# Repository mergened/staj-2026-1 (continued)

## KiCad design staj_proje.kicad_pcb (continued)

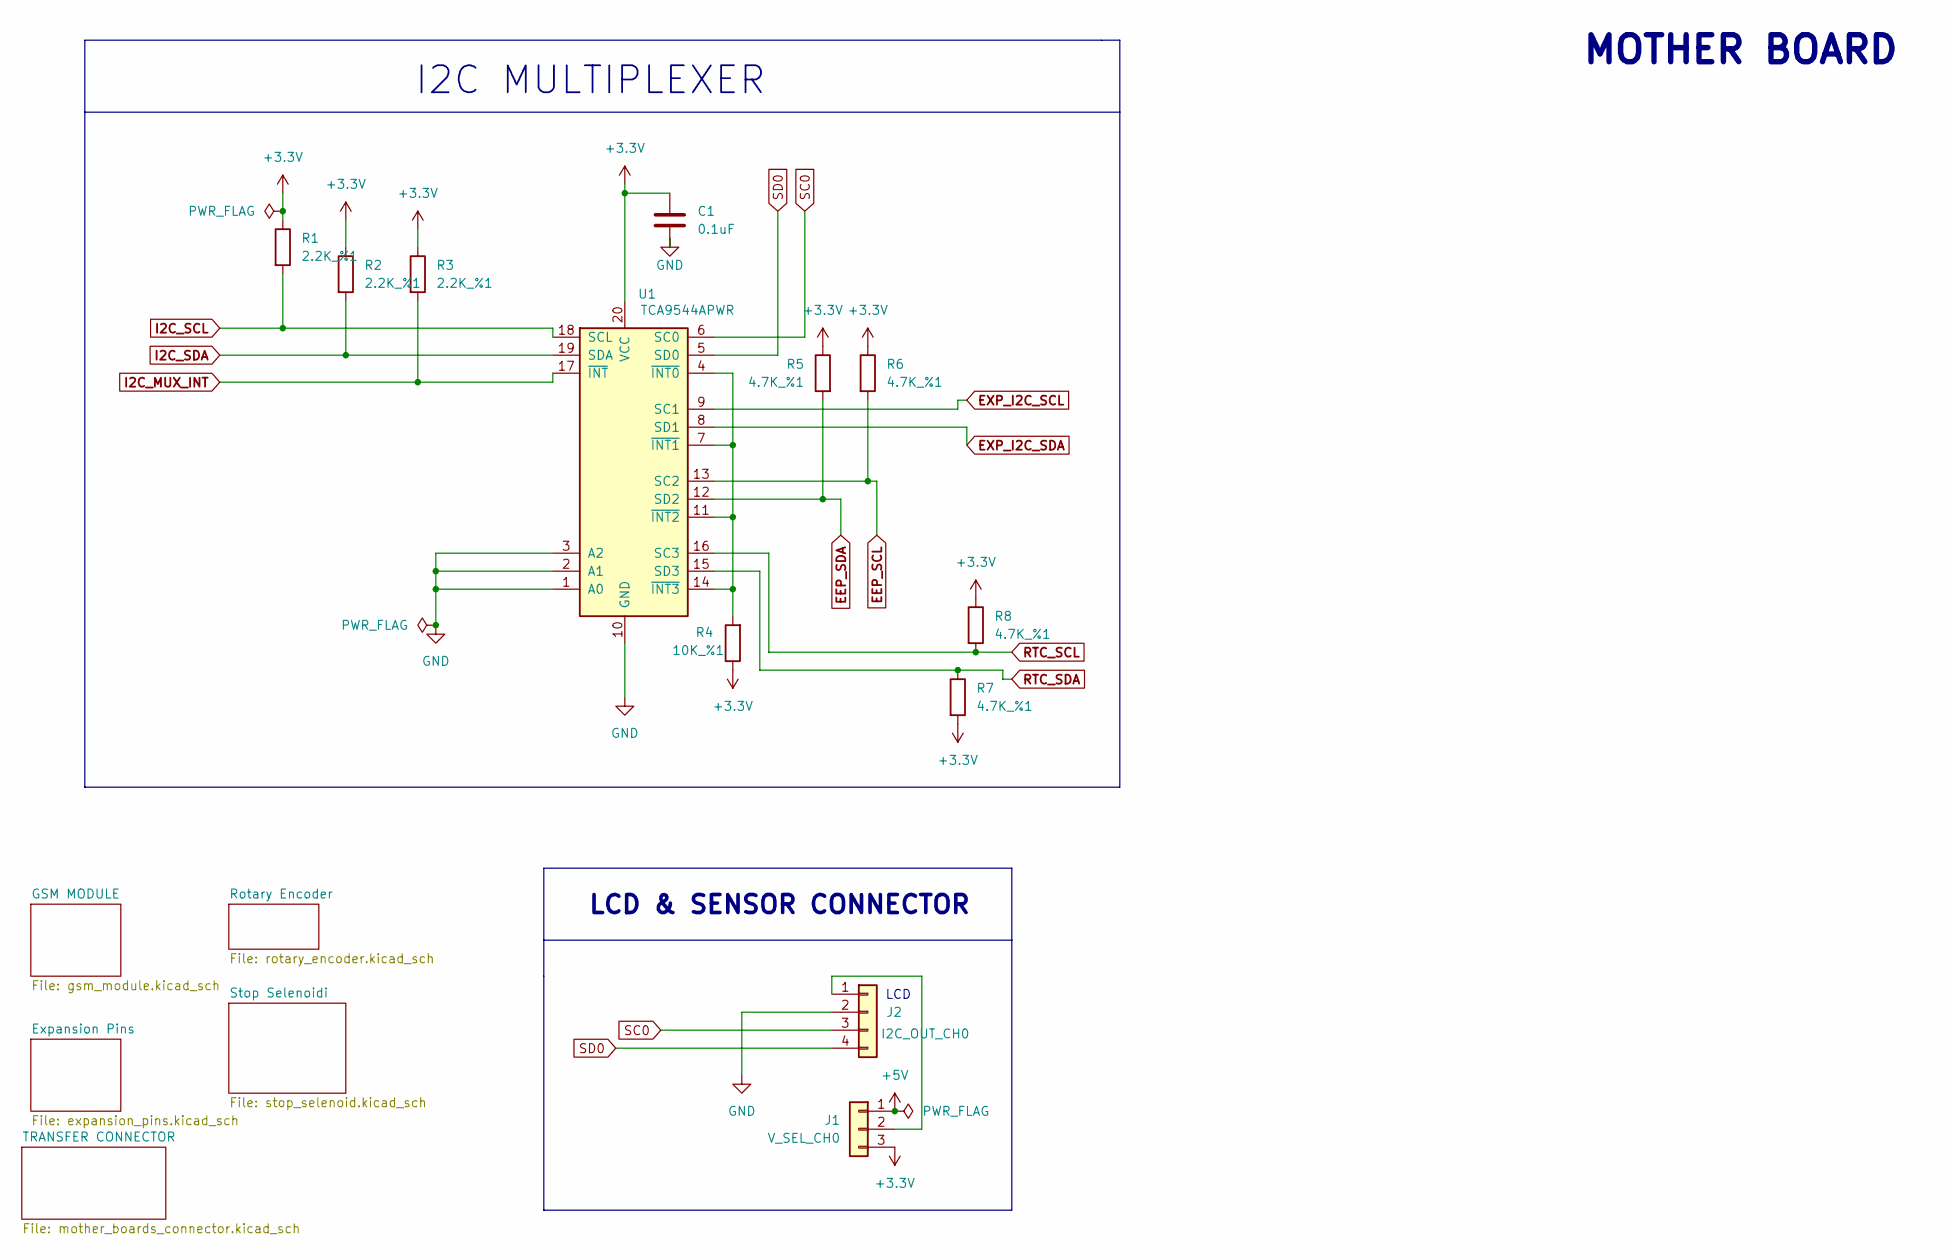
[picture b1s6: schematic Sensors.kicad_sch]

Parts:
C1: 0.1uF; C_0603_1608Metric; Manufacturer PN C0603C104K5RACTU; Digikey 399-C0603C104K5RACTUCT-ND
J1: V_SEL_CH0; PinHeader_1x03_P2.54mm_Vertical; Manufacturer PN G800W305018EU; Digikey 664-G800W305018EU-ND
J2: I2C_OUT_CH0; PinHeader_1x04_P2.54mm_Vertical; Manufacturer PN 10129378-904002BLF; Digikey 10129378-904002BLF-ND
R1, R2, R3: 2.2K_%1; R_0603_1608Metric; Manufacturer PN RC0603FR-072K2L; Digikey 311-2.20KHRCT-ND
R4: 10K_%1; R_0603_1608Metric; Manufacturer PN RC0603FR-0710KL; Digikey 311-10.0KHRCT-ND
R5, R6, R7, R8: 4.7K_%1; R_0603_1608Metric; Manufacturer PN RC0603FR-074K7L; Digikey 311-4.70KHRCT-ND
U1: TCA9544APWR; TSSOP-20_4.4x6.5mm_P0.65mm; Manufacturer PN TCA9544APWR; Digikey 296-40576-1-ND

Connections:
+3.3V: C1.1, J1.3, R1.1, R2.1, R3.1, R4.1, R5.1, R6.1, R7.2, R8.1, U1.20 (VCC); also elsewhere on the board
+5V: J1.1; also elsewhere on the board
EEP_SCL: R6.2, U1.13 (SC2); also elsewhere on the board
EEP_SDA: R5.2, U1.12 (SD2); also elsewhere on the board
EXP_I2C_SCL: U1.9 (SC1); also elsewhere on the board
EXP_I2C_SDA: U1.8 (SD1); also elsewhere on the board
GND: C1.2, J2.2, U1.1 (A0), U1.2 (A1), U1.3 (A2), U1.10 (GND); also elsewhere on the board
I2C_MUX_INT: R3.2, U1.17 (~INT); also elsewhere on the board
I2C_SCL: R1.2, U1.18 (SCL); also elsewhere on the board
I2C_SDA: R2.2, U1.19 (SDA); also elsewhere on the board
unnamed: J1.2, J2.1
unnamed: R4.2, U1.4 (~INT0), U1.7 (~INT1), U1.11 (~INT2), U1.14 (~INT3)
RTC_SCL: R8.2, U1.16 (SC3); also elsewhere on the board
RTC_SDA: R7.1, U1.15 (SD3); also elsewhere on the board
SC0: J2.3, U1.6 (SC0); also elsewhere on the board
SD0: J2.4, U1.5 (SD0); also elsewhere on the board

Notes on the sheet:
LCD
MOTHER BOARD
LCD & SENSOR CONNECTOR
I2C MULTIPLEXER

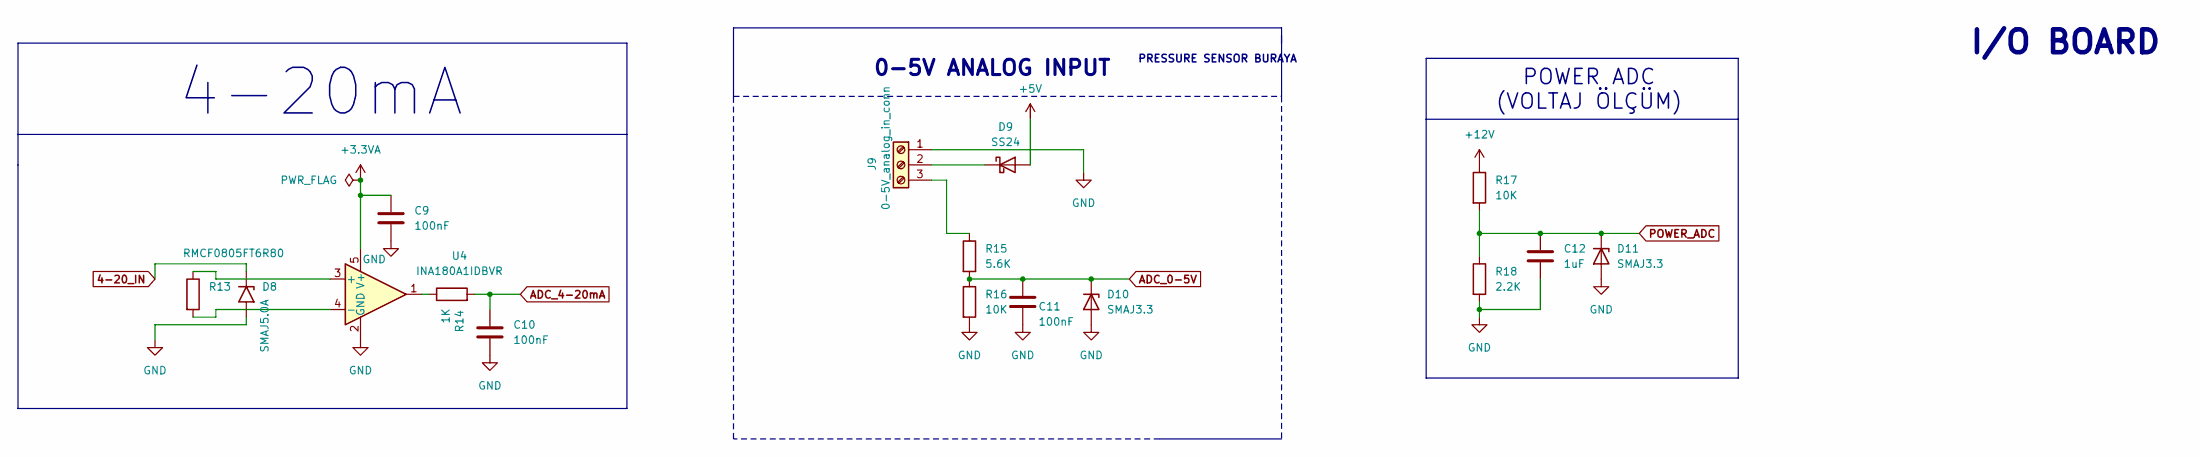
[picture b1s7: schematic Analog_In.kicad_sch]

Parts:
C9, C10, C11: 100nF; C_0603_1608Metric; Manufacturer PN E0603X7R104K500NTD; Digikey 3372-E0603X7R104K500NTDTR-ND
C12: 1uF; C_0603_1608Metric; Manufacturer PN GMC10X5R105M50NT; Digikey 2571-GMC10X5R105M50NTTR-ND
D8: SMAJ5.0A; D_SMA; Manufacturer PN SMAJ5.0A; Digikey SMAJ5.0ABCT-ND
D9: SS24; D_SMB; Manufacturer PN SS24; Digikey 1801-SS24CT-ND
D10, D11: SMAJ3.3; D_SMA; Manufacturer PN SMAJ33; Digikey 1801-SMAJ33TR-ND
J9: 0-5V_analog_in_conn; PhoenixContact_MC_1,5_3-G-5.08_1x03_P5.08mm_Horizontal; Manufacturer PN 1803280; Digikey 277-1207-ND
R13: RMCF0805FT6R80; R_0805_2012Metric; Manufacturer PN RMCF0805FT6R80; Digikey RMCF0805FT6R80CT-ND
R14: 1K; R_0603_1608Metric; Manufacturer PN RC0603FR-071KL; Digikey 311-1.00KHRCT-ND
R15: 5.6K; R_0603_1608Metric; Manufacturer PN RC0603FR-075K6L; Digikey 311-5.60KHRCT-ND
R16, R17: 10K; R_0603_1608Metric; Manufacturer PN RC0603FR-0710KL; Digikey 311-10.0KHRCT-ND
R18: 2.2K; R_0603_1608Metric; Manufacturer PN RC0603FR-072K2L; Digikey 311-2.20KHRCT-ND
U4: INA180A1IDBVR; SOT-23-5; Manufacturer PN INA180A1IDBVR; Digikey 296-47652-1-ND

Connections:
4-20_IN: D8.1 (A1); also elsewhere on the board
+3.3VA: C9.1, U4.5 (V+); also elsewhere on the board
+5V: D9.2 (A); also elsewhere on the board
+12V: R17.1; also elsewhere on the board
ADC_0-5V: C11.1, D10.1 (K), R15.2, R16.1; also elsewhere on the board
ADC_4-20mA: C10.1, R14.2; also elsewhere on the board
GND: C9.2, C10.2, C11.2, C12.2, D8.2 (A2), D10.2 (A), D11.2 (A), J9.1, R16.2, R18.2, U4.2 (GND); also elsewhere on the board
unnamed: D9.1 (K), J9.2
unnamed: J9.3, R15.1
unnamed: R14.1, U4.1
unnamed: R13.1, U4.3 (+)
unnamed: R13.2, U4.4 (-)
POWER_ADC: C12.1, D11.1 (K), R17.2, R18.1; also elsewhere on the board

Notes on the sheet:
4-20mA
PRESSURE SENSOR BURAYA
I/O BOARD
POWER ADC (VOLTAJ ÖLÇÜM)
0-5V ANALOG INPUT

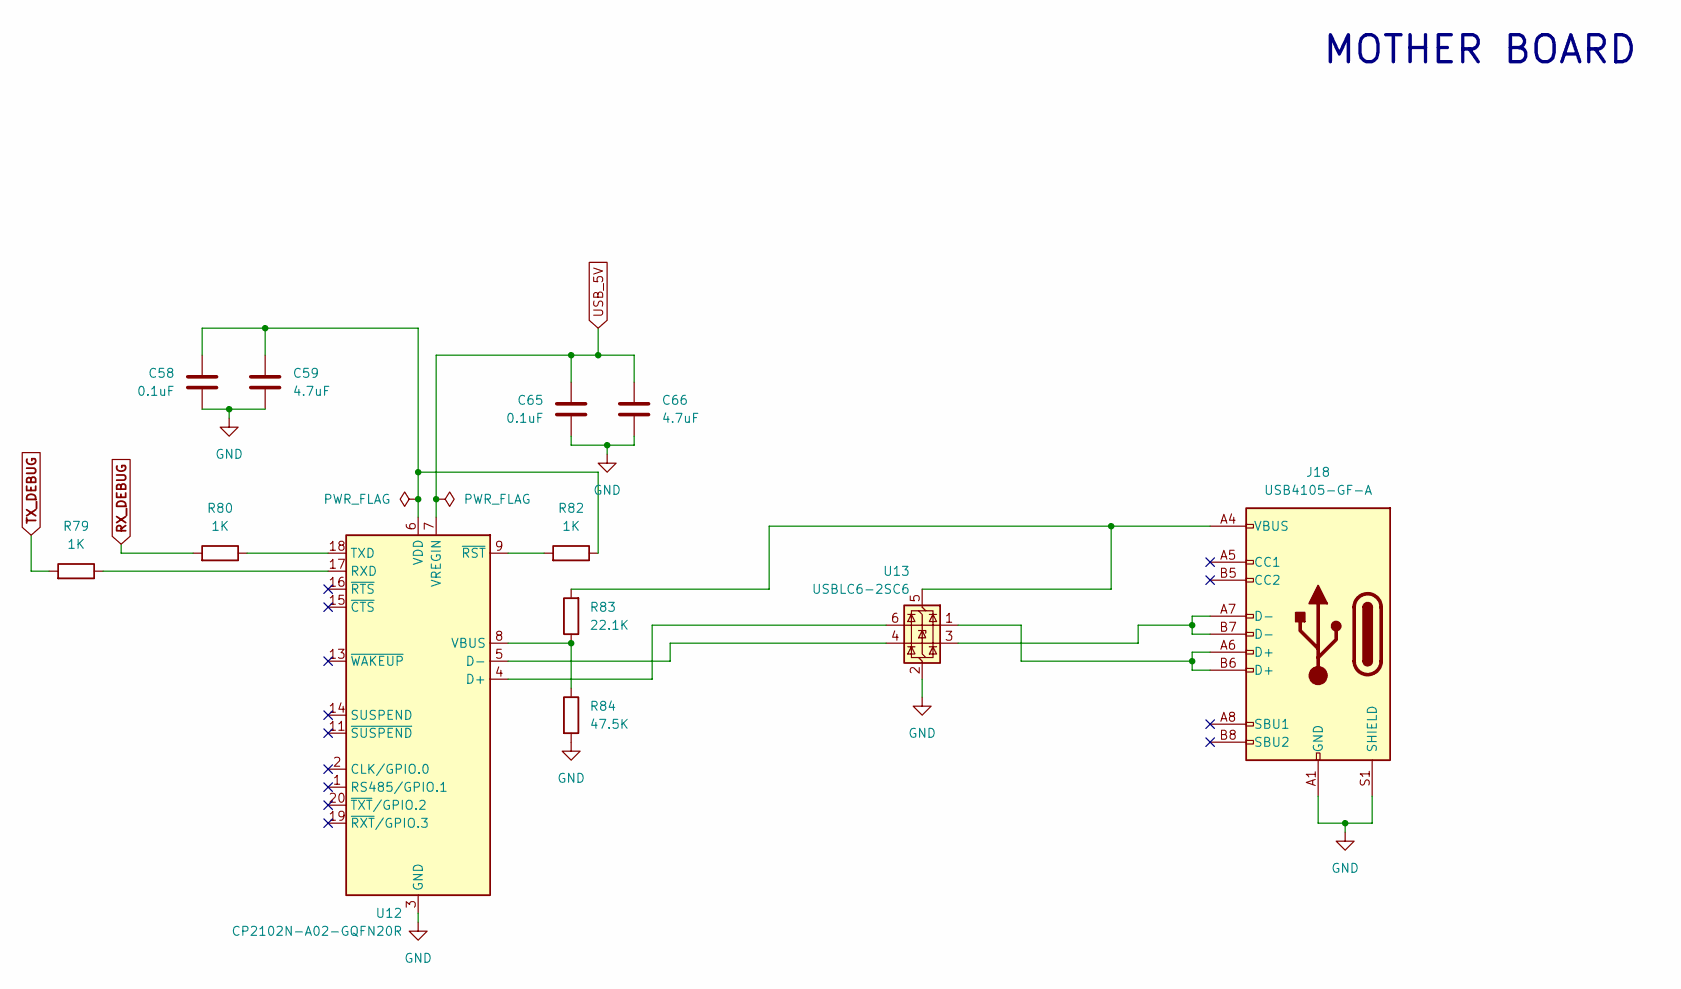
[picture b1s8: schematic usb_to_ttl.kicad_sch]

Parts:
C58, C65: 0.1uF; C_0603_1608Metric; Manufacturer PN C0603C104K5RACTU; Digikey 399-C0603C104K5RACTUCT-ND
C59, C66: 4.7uF; C_0603_1608Metric; Manufacturer PN CL10A475KO8NNNC; Digikey 1276-1784-1-ND
J18: USB4105-GF-A; USB_C_Receptacle_GCT_USB4105-xx-A_16P_TopMnt_Horizontal; Manufacturer PN USB4105-GF-A; Digikey 2073-USB4105-GF-ACT-ND
R79, R80, R82: 1K; R_0603_1608Metric; Manufacturer PN RMCF0603FT1K00; Digikey RMCF0603FT1K00CT-ND
R83: 22.1K; R_0603_1608Metric; Manufacturer PN RC0603FR-0722K1L; Digikey 311-22.1KHRCT-ND
R84: 47.5K; R_0603_1608Metric; Manufacturer PN RMCF0603FT47K5; Digikey RMCF0603FT47K5CT-ND
U12: CP2102N-A02-GQFN20R; QFN-20-1EP_3x3mm_P0.4mm_EP1.65x1.65mm; Manufacturer PN CP2102N-A02-GQFN20R; Digikey 336-5886-1-ND
U13: USBLC6-2SC6; SOT-23-6; Manufacturer PN USBLC6-2SC6; Digikey 497-5235-1-ND

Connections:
GND: C58.2, C59.1, C65.2, C66.1, J18.A1 (GND), J18.A12 (GND), J18.B1 (GND), J18.B12 (GND), J18.S1 (SHIELD), R84.2, U12.3 (GND), U12.12 (GND), U12.21 (GND), U13.2 (GND); also elsewhere on the board
unnamed: J18.A6 (D+), J18.B6 (D+), U13.1 (I/O1)
unnamed: J18.A7 (D-), J18.B7 (D-), U13.3 (I/O2)
unnamed: U12.4 (D+), U13.6 (I/O1)
unnamed: U12.5 (D-), U13.4 (I/O2)
unnamed: R79.1, U12.17 (RXD)
unnamed: R80.1, U12.18 (TXD)
unnamed: R83.1, R84.1, U12.8 (VBUS)
unnamed: C58.1, C59.2, R82.1, U12.6 (VDD)
unnamed: R82.2, U12.9 (~RST)
unnamed: J18.A4 (VBUS), J18.A9 (VBUS), J18.B4 (VBUS), J18.B9 (VBUS), R83.2, U13.5 (VBUS)
RX_DEBUG: R80.2; also elsewhere on the board
TX_DEBUG: R79.2; also elsewhere on the board
USB_5V: C65.1, C66.2, U12.7 (VREGIN)

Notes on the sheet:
MOTHER BOARD

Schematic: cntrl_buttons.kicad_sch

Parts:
C37, C38, C39, C40: 100nF; C_0603_1608Metric; Manufacturer PN E0603X7R104K500NTD; Digikey 3372-E0603X7R104K500NTDTR-ND
R46, R47, R48, R49: 10K; R_0603_1608Metric; Manufacturer PN RC0603FR-0710KL; Digikey 311-10.0KHRCT-ND
SW4: BTN_RIGHT; SW_PUSH_6mm; Manufacturer PN B3FS-1002P; Digikey SW424CT-ND; not fitted
SW5: BTN_UP; SW_PUSH_6mm; Manufacturer PN B3FS-1002P; Digikey SW424CT-ND; not fitted
SW6: BTN_DOWN; SW_PUSH_6mm; Manufacturer PN B3FS-1002P; Digikey SW424CT-ND; not fitted
SW7: BTN_LEFT; SW_PUSH_6mm; Manufacturer PN B3FS-1002P; Digikey SW424CT-ND; not fitted

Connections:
+3.3V: R46.1, R47.1, R48.1, R49.1; also elsewhere on the board
BTN_DOWN: C40.1, R48.2, SW6.2; also elsewhere on the board
BTN_LEFT: C38.1, R49.2, SW7.2; also elsewhere on the board
BTN_RIGHT: C37.1, R46.2, SW4.2; also elsewhere on the board
BTN_UP: C39.1, R47.2, SW5.2; also elsewhere on the board
GND: C37.2, C38.2, C39.2, C40.2, SW4.1, SW5.1, SW6.1, SW7.1; also elsewhere on the board

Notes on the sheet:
LCD AND BUTTON BOARD

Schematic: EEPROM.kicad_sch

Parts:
C33: 100nF; C_0603_1608Metric; Manufacturer PN E0603X7R104K500NTD; Digikey 3372-E0603X7R104K500NTDTR-ND
U9: CAT24C256WI-GT3; SOIC-8_3.9x4.9mm_P1.27mm; Manufacturer PN CAT24C256WI-GT3; Digikey CAT24C256WI-GT3OSCT-ND

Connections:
+3.3V: C33.1, U9.8 (VCC); also elsewhere on the board
EEP_SCL: U9.6 (SCL); also elsewhere on the board
EEP_SDA: U9.5 (SDA); also elsewhere on the board
EEP_WP: U9.7 (WP); also elsewhere on the board
GND: C33.2, U9.1 (A0), U9.2 (A1), U9.3 (A2), U9.4 (GND); also elsewhere on the board

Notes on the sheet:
MOTHER BOARD

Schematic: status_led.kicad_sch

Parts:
D18, D19, D20: LED; LED_0603_1608Metric; Manufacturer PN XL-1608SURC-06; Digikey 5962-XL-1608SURC-06TR-ND
R35, R36, R37: 330R; R_0603_1608Metric; Manufacturer PN RC0603FR-07330RL; Digikey 311-330HRCT-ND

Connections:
GND: D18.1 (K), D19.1 (K), D20.1 (K); also elsewhere on the board
LED_ERR: R37.2; also elsewhere on the board
LED_PWR: R35.2; also elsewhere on the board
LED_STAT: R36.2; also elsewhere on the board
unnamed: D18.2 (A), R35.1
unnamed: D19.2 (A), R36.1
unnamed: D20.2 (A), R37.1

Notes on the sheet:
MOTHER BOARD
STATUS LED

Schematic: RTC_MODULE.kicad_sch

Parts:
BT1: Battery_Cell; BAT_1056; Manufacturer PN 1056; Digikey 36-1056-ND
C20: 100nF; C_0603_1608Metric; Manufacturer PN E0603X7R104K500NTD; Digikey 3372-E0603X7R104K500NTDTR-ND
D17: BAS40-05; SOT-23; Manufacturer PN BAS40-05; Digikey 5399-BAS40-05CT-ND
R30, R33, R34: 4.7K; R_0603_1608Metric; Manufacturer PN RC0603FR-074K7L; Digikey 311-4.70KHRCT-ND
TP1: TestPoint; TestPoint_Pad_2.5x2.5mm
U7: DS3231MZ; SOIC-8_3.9x4.9mm_P1.27mm; Manufacturer PN DS3231MZ+; Digikey DS3231MZ+-ND

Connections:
+3.3V: C20.1, D17.2, R30.1, R33.1, R34.1, U7.2 (VCC); also elsewhere on the board
GND: BT1.2 (-), C20.2, U7.5 (GND); also elsewhere on the board
unnamed: BT1.1 (+), D17.1
unnamed: R34.2, TP1.1, U7.1 (32KHZ)
RTC_ALARM: R33.2, U7.3 (~INT/SQW); also elsewhere on the board
RTC_RST: R30.2, U7.4 (~RST); also elsewhere on the board
RTC_SCL: U7.8 (SCL); also elsewhere on the board
RTC_SDA: U7.7 (SDA); also elsewhere on the board
VBAT: D17.3, U7.6 (VBAT); also elsewhere on the board

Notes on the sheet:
MOTHER BOARD

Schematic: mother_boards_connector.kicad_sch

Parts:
J19: MB-GSM_CONN_1_MALE; IDC-Header_2x10_P2.54mm_Horizontal; Manufacturer PN SBH11-PBPC-D10-RA-BK; Digikey S9180-ND
J21: MB-IO_CONN_1_FEMALE; PinSocket_2x10_P2.54mm_Vertical; Manufacturer PN PPPC102LFBN-RC; Digikey S6106-ND
J23: MB-BUTT_CONN_1_MALE; PinHeader_2x10_P2.54mm_Vertical; Manufacturer PN 67996-420HLF; Digikey 609-3221-ND
J24: MB-IO_CONN_2_FEMALE; PinSocket_2x10_P2.54mm_Vertical; Manufacturer PN PPPC102LFBN-RC; Digikey S6106-ND

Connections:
+3.3V: J19.5, J19.6, J21.7, J21.8, J23.5, J23.6, J23.7, J23.8, J24.7, J24.8; also elsewhere on the board
+3.3VA: J21.9, J21.10, J24.9, J24.10; also elsewhere on the board
+5V: J19.1, J19.2, J21.5, J21.6, J23.1, J23.2, J24.5, J24.6; also elsewhere on the board
+12V: J21.1, J21.2, J24.1, J24.2; also elsewhere on the board
ADC_0-5V: J24.20; also elsewhere on the board
ADC_4-20mA: J24.17; also elsewhere on the board
BTN_DOWN: J23.20; also elsewhere on the board
BTN_LEFT: J23.17; also elsewhere on the board
BTN_RIGHT: J23.18; also elsewhere on the board
BTN_UP: J23.19; also elsewhere on the board
DIG_IN1: J21.18; also elsewhere on the board
DIG_IN2: J21.20; also elsewhere on the board
GND: J19.3, J19.4, J19.7, J19.8, J19.19, J19.20, J21.3, J21.4, J21.11, J21.12, J21.19, J23.3, J23.4, J23.9, J23.10, J23.11, J23.12, J23.15, J23.16, J24.3, J24.4, J24.11, J24.12; also elsewhere on the board
GPIO_PIN_MOTOR_1: J24.13; also elsewhere on the board
GPIO_PIN_MOTOR_2: J24.15; also elsewhere on the board
GPIO_PIN_MOTOR_3: J24.16; also elsewhere on the board
GPIO_PIN_MOTOR_4: J24.18; also elsewhere on the board
GSM_CTS: J19.16; also elsewhere on the board
GSM_PWRKY: J19.13; also elsewhere on the board
GSM_RST: J19.15; also elsewhere on the board
GSM_RTS: J19.14; also elsewhere on the board
GSM_RX: J19.12; also elsewhere on the board
GSM_TX: J19.11; also elsewhere on the board
GSM_UART3_RX: J19.18; also elsewhere on the board
GSM_UART3_TX: J19.17; also elsewhere on the board
PE2: J24.14; also elsewhere on the board
POWER_ADC: J24.19; also elsewhere on the board
PULSE_1: J21.14; also elsewhere on the board
PULSE_2: J21.16; also elsewhere on the board
RS485_DIR: J21.13; also elsewhere on the board
RS485_RX: J21.15; also elsewhere on the board
RS485_TX: J21.17; also elsewhere on the board
SC0: J23.13; also elsewhere on the board
SD0: J23.14; also elsewhere on the board
UART_LOG_RX: J19.10; also elsewhere on the board
UART_LOG_TX: J19.9; also elsewhere on the board

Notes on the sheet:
FEMALE CONNECTORS
GSM
2.KAT KART
MOTHER BOARD

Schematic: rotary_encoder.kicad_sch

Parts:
C34, C35: 100nF; C_0603_1608Metric; Manufacturer PN E0603X7R104K500NTD; Digikey 3372-E0603X7R104K500NTDTR-ND; not fitted
C36: 1uF; C_0603_1608Metric; Manufacturer PN 0603B105K100XD; Digikey 3372-0603B105K100XDTR-ND; not fitted
J14: conn_rotaryencoder; Molex_KK-254_AE-6410-05A_1x05_P2.54mm_Vertical; Manufacturer PN 0022232051; Digikey WM4203-ND; not fitted
R40, R41, R45: 1K_%1; R_0603_1608Metric; Manufacturer PN RMCF0603FT1K00; Digikey RMCF0603FT1K00CT-ND; not fitted
R42, R43, R44: 10K_%1; R_0603_1608Metric; Manufacturer PN RC0603FR-0710KL; Digikey 311-10.0KHRCT-ND; not fitted
SW3: RotaryEncoder_Switch; XDCR_PEC11R-4215F-S0024; Manufacturer PN PEC11R-4215F-S0024; Digikey PEC11R-4215F-S0024-ND; not fitted

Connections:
unnamed: C34.1, J14.1, R40.2, R42.2
unnamed: C35.1, J14.2, R41.2, R43.2
unnamed: C36.1, J14.3, R44.2, R45.1

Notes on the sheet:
LCD AND CONTROL BOARD

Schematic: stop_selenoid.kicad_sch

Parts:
D21, D23: SS24; D_SMB; Manufacturer PN SS24; Digikey 1801-SS24CT-ND
D22: S3M; D_SMC; Manufacturer PN S3M; Digikey S3MFSCT-ND
J13: stopselenoid_klemens; PhoenixContact_MC_1,5_3-G-5.08_1x03_P5.08mm_Horizontal; Manufacturer PN 1803280; Digikey 277-1207-ND
K5: ALQ3F12; Manufacturer PN ALQ3F12; Digikey 255-5407-ND
Q5: BC817; SOT-23-3; Manufacturer PN BC817-16-7; Digikey BC817-16-7-ND
R38: 1K_%1; R_0603_1608Metric; Manufacturer PN RMCF0603FT1K00; Digikey RMCF0603FT1K00CT-ND
R39: 10K_%1; R_0603_1608Metric; Manufacturer PN RC0603FR-0710KL; Digikey 311-10.0KHRCT-ND

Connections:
+12V: D21.2 (A), D23.1 (K), K5.1, K5.3; also elsewhere on the board
GND: D22.2 (A), J13.1, Q5.2 (E), R39.1; also elsewhere on the board
unnamed: D21.1 (K), J13.3
unnamed: D22.1 (K), J13.2, K5.4
unnamed: D23.2 (A), K5.2, Q5.3 (C)
unnamed: Q5.1 (B), R38.1
PE2: R38.2, R39.2; also elsewhere on the board

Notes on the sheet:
I/O BOARD
STOP SELENOİD UCU

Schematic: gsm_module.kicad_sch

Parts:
C41: 470pF_NM; C_0603_1608Metric; Manufacturer PN Do Not Populate; Digikey Do Not Populate; not fitted
C42, C43, C44, C51, C52: 1nF; C_0603_1608Metric; Manufacturer PN 0603B102K101SD; Digikey 3372-0603B102K101SDTR-ND
C45: 10pF; C_0603_1608Metric; Manufacturer PN C0603C100K5GACTU; Digikey 399-C0603C100K5GACTUCT-ND
C46: 33pF; C_0603_1608Metric; Manufacturer PN C0603C330M5HACTU; Digikey 399-C0603C330M5HACTUCT-ND
C47: 0.1uF; C_0603_1608Metric; Manufacturer PN C0603C104K5RACTU; Digikey 399-C0603C104K5RACTUCT-ND
C48: 1uF; C_0603_1608Metric; Manufacturer PN 0603B105K100XD; Digikey 3372-0603B105K100XDTR-ND
C49, C50: 100uF; C_1210_3225Metric; Manufacturer PN 0603B102K101SD; Digikey 587-5426-1-ND
C53: 470pF_NM; C_0603_1608Metric; Manufacturer PN Do Not Populate; Digikey Do Not Populate
D24: LED; LED_0603_1608Metric; Manufacturer PN LTST-C190TBKT; Digikey 160-1646-1-ND
D25: LED; LED_0603_1608Metric; Manufacturer PN LTST-C190KGKT; Digikey 160-1435-1-ND
D26, D27, D28, D29, D33: TPD1E10B06DPYR; D_0402_1005Metric; Manufacturer PN TPD1E10B06DPYR; Digikey 296-30406-1-ND
D30, D31, D32: PESD3V3L1UB,115; D_SOD-523; Manufacturer PN PESD3V3L1UB,115; Digikey 1727-5418-1-ND
D34, D35: ESD9L5.0ST5G; D_SOD-923; Manufacturer PN ESD9L5.0ST5G; Digikey ESD9L5.0ST5GOSCT-ND
FB2: BLM21PG300SN1D; C_0805_2012Metric; Manufacturer PN BLM21PG300SN1D; Digikey 490-1052-1-ND
J16: DEBUG UART; PinHeader_1x03_P2.54mm_Vertical; Manufacturer PN 61300311121; Digikey 732-5316-ND
Q6, Q7, Q10, Q11: MMBT3904; SOT-23-3; Manufacturer PN MMBT3904; Digikey MMBT3904FSTR-ND
Q8, Q9, Q12, Q13: BC817; SOT-23-3; Manufacturer PN BC817-16-7; Digikey BC817-16-7-ND
R50, R51, R52, R55, R56, R60, R68, R69, R70, R71, R72, R75: 4.7K_%1; R_0603_1608Metric; Manufacturer PN RC0603FR-074K7L; Digikey 311-4.70KHRCT-ND
R53, R54, R73, R74: 47K_%1; R_0603_1608Metric; Manufacturer PN RC0603FR-0747KL; Digikey 311-47.0KHRCT-ND
R57, R61, R62: 0R_NM; R_0603_1608Metric; Manufacturer PN Do Not Populate; Digikey Do Not Populate
R58, R59: 330R_%1; R_0603_1608Metric; Manufacturer PN RC0603FR-07330RL; Digikey 311-330HRCT-ND
R63: 10K; R_0603_1608Metric; Manufacturer PN RC0603FR-0710KL; Digikey 311-10.0KHRCT-ND
R64, R65: 0R; R_0603_1608Metric; Manufacturer PN ANTISULF RES0603 1% 0 OHM; Digikey 4713-CAS06F0000CT-ND
R66: 680K; R_0603_1608Metric; Manufacturer PN RMCF0603FT680K; Digikey RMCF0603FT680KCT-ND
R67: 470K; R_0603_1608Metric; Manufacturer PN RC0603FR-07470KL; Digikey 311-470KHRCT-ND
SW8: SW_Push; SW_PUSH_6mm; Manufacturer PN B3FS-1002P; Digikey SW424CT-ND; not fitted
TP2: TP_VBUS; TestPoint_Pad_2.5x2.5mm
TP3: GND_TP; TestPoint_Pad_2.5x2.5mm
TP4: TP_USB_DM; TestPoint_Pad_2.5x2.5mm
TP_USB_DP1: TestPoint; TestPoint_Pad_2.5x2.5mm
U10: SIMCOM A7672E FASE; A7672E; Manufacturer PN A7672E (FASE); Digikey 3781-A7672E(FASE)-ND

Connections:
+3.3V: C41.1, C53.1, R50.1, R75.1; also elsewhere on the board
BT_ANTENNA: U10.93 (BT_ANT); also elsewhere on the board
GND: C44.2, C45.2, C46.2, C47.2, C48.2, C49.2, C50.2, D26.1 (A1), D27.1 (A1), D28.1 (A1), D29.1 (A1), D30.1 (A1), D31.1 (A1), D32.1 (A1), D33.2 (A2), D34.1 (A1), D35.1 (A1), J16.1, Q8.2 (E), Q9.2 (E), Q12.2 (E), Q13.2 (E), R53.2, R54.2, R67.1, R73.2, R74.2, TP3.1, U10.2 (GND), U10.17 (GND), U10.18 (GND), U10.29 (GND), U10.39 (GND), U10.45 (GND), U10.46 (GND), U10.54 (GND), U10.58 (GND), U10.59 (GND), U10.61 (GND), U10.62 (GND), U10.63 (GND), U10.64 (GND), U10.65 (GND), U10.69 (GND), U10.70 (GND), U10.71 (GND), U10.72 (GND), U10.73 (GND), U10.74 (GND), U10.75 (GND), U10.76 (GND), U10.77 (GND), U10.78 (GND), U10.79 (GND), U10.80 (GND), U10.81 (GND), U10.82 (GND), U10.83 (GND), U10.84 (GND), U10.85 (GND), U10.86 (GND), U10.87 (GND), U10.88 (GND), U10.89 (GND), U10.91 (GND), U10.92 (GND), U10.94 (GND); also elsewhere on the board
GSM_CTS: U10.7 (CTS); also elsewhere on the board
GSM_PWRKY: R69.1; also elsewhere on the board
GSM_RST: R72.1; also elsewhere on the board
GSM_RTS: U10.8 (RTS); also elsewhere on the board
GSM_RX: C41.2, Q6.3 (C), R50.2; also elsewhere on the board
GSM_TX: Q7.2 (E); also elsewhere on the board
GSM_UART3_RX: Q11.2 (E); also elsewhere on the board
GSM_UART3_TX: C53.2, Q10.3 (C), R75.2; also elsewhere on the board
G_PWRKY: D34.2 (A2), Q12.3 (C), U10.1 (PWRKEY)
G_RST: D35.2 (A2), Q13.3 (C), U10.16 (RESET)
NETLIGHT_GSM: R51.1, U10.52 (NETLIGHT)
unnamed: C45.1, C46.1, C47.1, C48.1, C49.1, C50.1, FB2.2, U10.55 (VBAT), U10.56 (VBAT), U10.57 (VBAT)
unnamed: D24.1 (K), R58.1
unnamed: D25.1 (K), R59.1
unnamed: D26.2 (A2), R57.2, U10.24 (VBUS)
unnamed: D27.2 (A2), R61.2, U10.27 (USB_DP)
unnamed: D28.2 (A2), R62.2, U10.28 (USB_DM)
unnamed: D29.2 (A2), SW8.1, U10.6 (USB_BOOT)
unnamed: C43.1, Q6.1 (B), R55.2
unnamed: Q6.2 (E), U10.9 (TXD)
unnamed: C42.2, Q7.1 (B), R56.1
unnamed: Q7.3 (C), R60.1, U10.10 (RXD)
unnamed: Q8.1 (B), R51.2, R53.1
unnamed: Q8.3 (C), R58.2
unnamed: Q9.1 (B), R52.2, R54.1
unnamed: Q9.3 (C), R59.2
unnamed: C51.1, Q10.1 (B), R70.2
unnamed: Q10.2 (E), U10.49 (UART3_RXD)
unnamed: C52.2, Q11.1 (B), R71.1
unnamed: Q11.3 (C), R68.1, U10.50 (UART3_TXD)
unnamed: Q12.1 (B), R69.2, R73.1
unnamed: Q13.1 (B), R72.2, R74.1
unnamed: R57.1, TP2.1
unnamed: R61.1, TP_USB_DP1.1
unnamed: R62.1, TP4.1
unnamed: R63.1, SW8.2
unnamed: R64.2, U10.22 (UART_LOG_RX)
unnamed: R65.2, U10.23 (UART_LOG_TX)
unnamed: C44.1, R66.2, R67.2, U10.51 (VBAT_ADC)
RF_ANTEN: U10.60 (RF_ANT); also elsewhere on the board
SIM_CLK: U10.32 (USIM1_CLK); also elsewhere on the board
SIM_DATA: U10.31 (USIM1_DATA); also elsewhere on the board
SIM_RST: U10.33 (USIM1_RST); also elsewhere on the board
SIM_VDD: U10.30 (USIM1_VDD); also elsewhere on the board
STATUS_GSM: R52.1, U10.66 (STATUS)
UART_LOG_RX: D30.2 (A2), J16.3, R64.1; also elsewhere on the board
UART_LOG_TX: D31.2 (A2), J16.2, R65.1; also elsewhere on the board
VBAT_GSM: D24.2 (A), D25.2 (A), D33.1 (A1), FB2.1, R66.1; also elsewhere on the board
VDD_1V8: C42.1, C43.2, C51.2, C52.1, D32.2 (A2), R55.1, R56.2, R60.2, R63.2, R68.2, R70.1, R71.2, U10.15 (VDD_1V8)

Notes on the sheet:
GSM BOARD
MCU TARAFI
1.8V ONLY!
A7672E FASE
VIO_MCU:MCU VOLTAJINA GÖRE

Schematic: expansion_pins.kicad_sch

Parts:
J15: Expansion_Pins; IDC-Header_2x07_P2.54mm_Horizontal; Manufacturer PN 61201421721; Digikey 61201421721

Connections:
+3.3V: J15.3; also elsewhere on the board
+5V: J15.1; also elsewhere on the board
EXP_GPIO: J15.5; also elsewhere on the board
EXP_I2C_SCL: J15.10; also elsewhere on the board
EXP_I2C_SDA: J15.11; also elsewhere on the board
EXP_SPI_CS: J15.6; also elsewhere on the board
EXP_SPI_MISO: J15.8; also elsewhere on the board
EXP_SPI_MOSI: J15.9; also elsewhere on the board
EXP_SPI_SCK: J15.7; also elsewhere on the board
EXP_UART_RX: J15.13; also elsewhere on the board
EXP_UART_TX: J15.12; also elsewhere on the board
GND: J15.2, J15.4, J15.14; also elsewhere on the board

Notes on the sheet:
EXPANSİON PİNS
MOTHER BOARD

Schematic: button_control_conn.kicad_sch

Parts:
J27: MB-BUT_CONN_1_FEMALE; PinSocket_2x10_P2.54mm_Vertical; Manufacturer PN PPPC102LFBN-RC; Digikey S6106-ND

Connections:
+3.3V: J27.5, J27.6, J27.7, J27.8; also elsewhere on the board
+5V: J27.1, J27.2; also elsewhere on the board
BTN_DOWN: J27.20; also elsewhere on the board
BTN_LEFT: J27.17; also elsewhere on the board
BTN_RIGHT: J27.18; also elsewhere on the board
BTN_UP: J27.19; also elsewhere on the board
GND: J27.3, J27.4, J27.9, J27.10, J27.11, J27.12, J27.15, J27.16; also elsewhere on the board
SC0: J27.13; also elsewhere on the board
SD0: J27.14; also elsewhere on the board

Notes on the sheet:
FEMALE CONNECTORS
CONTROL AND BUTTONS BOARD

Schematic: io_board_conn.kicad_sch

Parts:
J25: I/O_CONN_1_MALE; PinHeader_2x10_P2.54mm_Vertical; Manufacturer PN 67996-420HLF; Digikey 609-3221-ND
J26: I/O_CONN_2_MALE; PinHeader_2x10_P2.54mm_Vertical; Manufacturer PN 67996-420HLF; Digikey 609-3221-ND

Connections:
+3.3V: J25.7, J25.8, J26.7, J26.8; also elsewhere on the board
+3.3VA: J25.9, J25.10, J26.9, J26.10; also elsewhere on the board
+5V: J25.5, J25.6, J26.5, J26.6; also elsewhere on the board
+12V: J25.1, J25.2, J26.1, J26.2; also elsewhere on the board
ADC_0-5V: J26.20; also elsewhere on the board
ADC_4-20mA: J26.17; also elsewhere on the board
DIG_IN1: J25.18; also elsewhere on the board
DIG_IN2: J25.20; also elsewhere on the board
GND: J25.3, J25.4, J25.11, J25.12, J25.19, J26.3, J26.4, J26.11, J26.12; also elsewhere on the board
GPIO_PIN_MOTOR_1: J26.13; also elsewhere on the board
GPIO_PIN_MOTOR_2: J26.15; also elsewhere on the board
GPIO_PIN_MOTOR_3: J26.16; also elsewhere on the board
GPIO_PIN_MOTOR_4: J26.18; also elsewhere on the board
PE2: J26.14; also elsewhere on the board
POWER_ADC: J26.19; also elsewhere on the board
PULSE_1: J25.14; also elsewhere on the board
PULSE_2: J25.16; also elsewhere on the board
RS485_DIR: J25.13; also elsewhere on the board
RS485_RX: J25.15; also elsewhere on the board
RS485_TX: J25.17; also elsewhere on the board

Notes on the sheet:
I/O BOARD
1.KAT KART

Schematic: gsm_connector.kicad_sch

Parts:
J28: MB-GSM_CONN_2_MALE; IDC-Header_2x10_P2.54mm_Horizontal; Manufacturer PN SBH11-PBPC-D10-RA-BK; Digikey S9180-ND

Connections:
+3.3V: J28.5, J28.6; also elsewhere on the board
+5V: J28.1, J28.2; also elsewhere on the board
GND: J28.3, J28.4, J28.7, J28.8, J28.19, J28.20; also elsewhere on the board
GSM_CTS: J28.16; also elsewhere on the board
GSM_PWRKY: J28.13; also elsewhere on the board
GSM_RST: J28.15; also elsewhere on the board
GSM_RTS: J28.14; also elsewhere on the board
GSM_RX: J28.12; also elsewhere on the board
GSM_TX: J28.11; also elsewhere on the board
GSM_UART3_RX: J28.18; also elsewhere on the board
GSM_UART3_TX: J28.17; also elsewhere on the board
UART_LOG_RX: J28.10; also elsewhere on the board
UART_LOG_TX: J28.9; also elsewhere on the board

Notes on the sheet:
CONTROL AND BUTTONS BOARD

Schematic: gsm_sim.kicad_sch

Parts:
C60: 33pF; C_0603_1608Metric; Manufacturer PN C0603C330M5HACTU; Digikey 399-C0603C330M5HACTUCT-ND
C61, C63, C64: 22pF_NM; C_0603_1608Metric; Manufacturer PN Do Not Populate; Digikey Do Not Populate; not fitted
C62: 100nF; C_0603_1608Metric; Manufacturer PN E0603X7R104K500NTD; Digikey 3372-E0603X7R104K500NTDTR-ND
D36: ESDA6V1SC5; SC-74A-5_1.55x2.9mm_P0.95mm; Manufacturer PN ESDA6V1SC5; Digikey 497-7748-1-ND
J17: 693021020811; Manufacturer PN 693021020811; Digikey 732-693021020811CT-ND
R81, R85, R86: 22R; R_0603_1608Metric; Manufacturer PN RMCF0603FT22R0; Digikey RMCF0603FT22R0CT-ND

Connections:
GND: C60.2, C61.2, C62.1, C63.2, C64.2, D36.2 (A), J17.C5 (GND), J17.S1, J17.S2, J17.S3, J17.S4; also elsewhere on the board
unnamed: D36.3 (K), J17.C3 (CLK), R85.1
unnamed: D36.1 (K), J17.C7 (I/O), R86.1
unnamed: D36.4 (K), J17.C2 (RST), R81.1
SIM_CLK: C63.1, R85.2; also elsewhere on the board
SIM_DATA: C64.1, R86.2; also elsewhere on the board
SIM_RST: C61.1, R81.2; also elsewhere on the board
SIM_VDD: C60.1, C62.2, D36.5 (K), J17.C1 (VCC); also elsewhere on the board

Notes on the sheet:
GSM SIM
GSM BOARD

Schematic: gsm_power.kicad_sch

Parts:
C54: 100uF; C_1210_3225Metric; Manufacturer PN 0603B102K101SD; Digikey 587-5426-1-ND
C55: 1uF; C_0603_1608Metric; Manufacturer PN GMC10X5R105M50NT; Digikey 2571-GMC10X5R105M50NTTR-ND
C56: 330uF; CP_Elec_10x10.5; Manufacturer PN EEE-FT1H331AP; Digikey PCE5026CT-ND
C57: 100nF; C_0603_1608Metric; Manufacturer PN E0603X7R104K500NTD; Digikey 3372-E0603X7R104K500NTDTR-ND
R76: 47K; R_0603_1608Metric; Manufacturer PN RC0603FR-0747KL; Digikey 311-47.0KHRCT-ND
R77: 100K; R_0603_1608Metric; Manufacturer PN RC0603FR-07100KL; Digikey 311-100KHRCT-ND
R78: 470R; R_0603_1608Metric; Manufacturer PN CRGCQ0603F470R; Digikey A129684CT-ND
U11: MIC29302WU; TO-263-5_TabPin3; Manufacturer PN MIC29302WU; Digikey 5399-MIC29302WUCT-ND

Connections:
+5V: C54.1, C55.1, U11.1 (EN), U11.2 (VIN); also elsewhere on the board
GND: C54.2, C55.2, C56.2, C57.2, R76.2, R78.2, U11.3 (GND); also elsewhere on the board
unnamed: R76.1, R77.2, U11.5 (ADJ)
VBAT_GSM: C56.1, C57.1, R77.1, R78.1, U11.4 (VOUT); also elsewhere on the board

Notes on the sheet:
GSM BOARD
GSM POWER MODULE

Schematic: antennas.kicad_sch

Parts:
C67, C68, C69, C70: NM; C_0603_1608Metric; Manufacturer PN Do Not Populate; Digikey Do Not Populate; not fitted
D37, D38: ESD9L3.3ST5G; D_SOD-923; Manufacturer PN ESD9L3.3ST5G; Digikey ESD9L3.3ST5GOSCT-ND
J20, J22: U.FL-R-SMT-1(10); U.FL_Hirose_U.FL-R-SMT-1_Vertical; Manufacturer PN U.FL-R-SMT-1(10); Digikey H11891CT-ND
R87, R88: 0R; R_0603_1608Metric; Manufacturer PN ANTISULF RES0603 1% 0 OHM; Digikey 4713-CAS06F0000CT-ND

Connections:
/Sensors_AND_Connectors_Sch/GSM MODULE/ANTENNAS/BF_2: C70.1, D38.2 (A2), J22.1 (In), R88.2
/Sensors_AND_Connectors_Sch/GSM MODULE/ANTENNAS/RF_2: C69.1, D37.2 (A2), J20.1 (In), R87.2
BT_ANTENNA: C68.1, R88.1; also elsewhere on the board
GND: C67.2, C68.2, C69.2, C70.2, D37.1 (A1), D38.1 (A1), J20.2 (Ext), J22.2 (Ext); also elsewhere on the board
RF_ANTEN: C67.1, R87.1; also elsewhere on the board

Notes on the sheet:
NON-STANDALONE RF ANTEN
NON-STANDALONE BLUETOOTH ANTEN
GSM BOARD

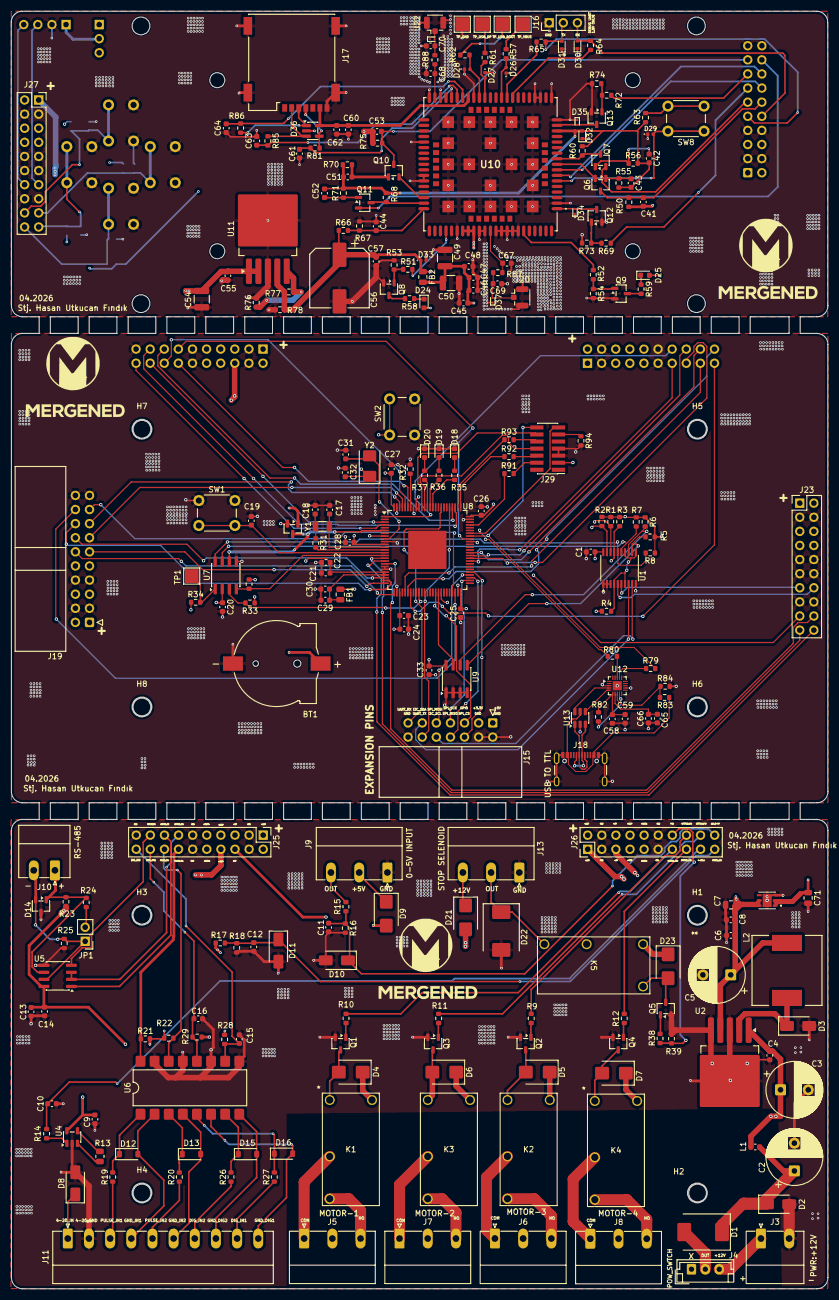
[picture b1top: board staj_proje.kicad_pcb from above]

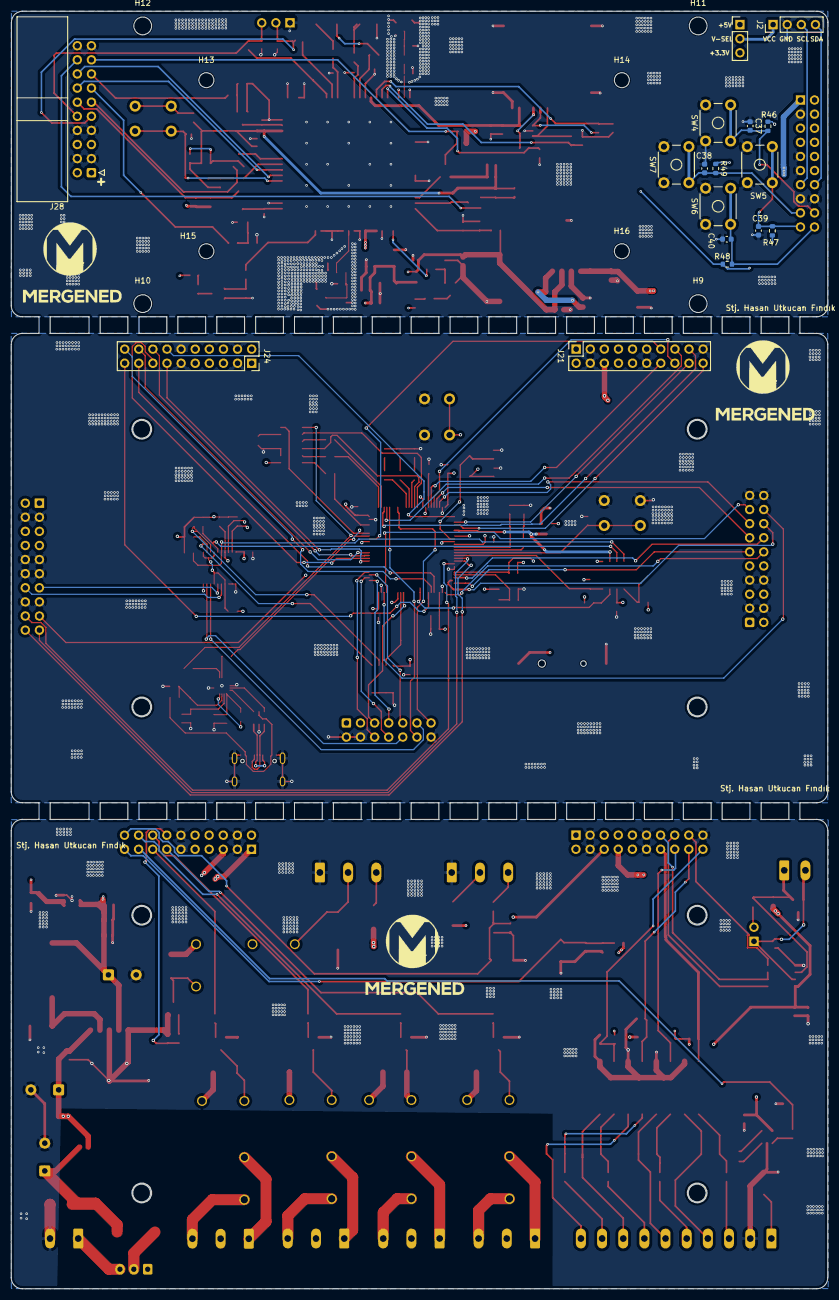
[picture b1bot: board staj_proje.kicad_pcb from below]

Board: 4 copper layers, 146.8 x 229.8 mm, 286 parts (25 on the bottom side), 186 nets.

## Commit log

2026-03-27 İlk PCB yerleşimi ve şematik yüklendi
    İnceleme için ana tasarım dosyaları eklendi.
2026-04-27 feat:Project version v1.0
